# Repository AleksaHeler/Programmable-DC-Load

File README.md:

# Programmable DC Load

Flexible programmable DC constant current/power load using Arduin Nano and a custom PCB.

Following some ideas from [this YouTube playlist](https://www.youtube.com/playlist?list=PLUMG8JNssPPzbr4LydbTcBrhoPlemu5Dt) from [Scullcom Hobby Electronics](https://www.youtube.com/@scullcomhobbyelectronics1702).

## PCB design and schematic

## Finished device in enclosure

## Programming the ATmega328P

### Setting the fuses

If you just want the same ones as used in a standard Arduino, you can find them in the ```boards.txt``` file:
```
uno.bootloader.low_fuses=0xff
uno.bootloader.high_fuses=0xde
uno.bootloader.extended_fuses=0x05
```

We will be using another Arduino as ISP, so we should first program it with given example code, then we can use avrdude option 'avrisp', and use the port number of that device. We can read the fuses, and check if conncections are ok with:
``` 
.\utils\avrdude-v8.0\avrdude.exe -c avrisp -p m328p -P com23 -b 19200 -U lfuse:r:-:i -U hfuse:r:-:i -U efuse:r:-:i -v
``` 

So for these default settings we would use the following command:
``` 
.\utils\avrdude-v8.0\avrdude.exe -c avrisp -p m328p -P com23 -b 19200 -U lfuse:w:0xFF:m -U hfuse:w:0xDE:m -U efuse:w:0x05:m -v
```
Where:
```
  -c <programmer>                          Specify programmer type.
  -p <partno>                              Required. Specify AVR device.
  -P <port>                                Specify connection port.
  -b <baudrate>                            Override RS-232 baud rate.
  -U <memtype>:r|w|v:<filename>[:format]   Memory operation specification.
  -v                                       Verbose output. -v -v for more.
```
More options info can be found [here](https://www.nongnu.org/avrdude/user-manual/avrdude_3.html).

### Burning the bootloader

To burn the bootloader, we will also be using Arduino as ISP, and in Arduino software just select burn bootloader after we select the board as Arduino Uno.

### Flashing the program

???

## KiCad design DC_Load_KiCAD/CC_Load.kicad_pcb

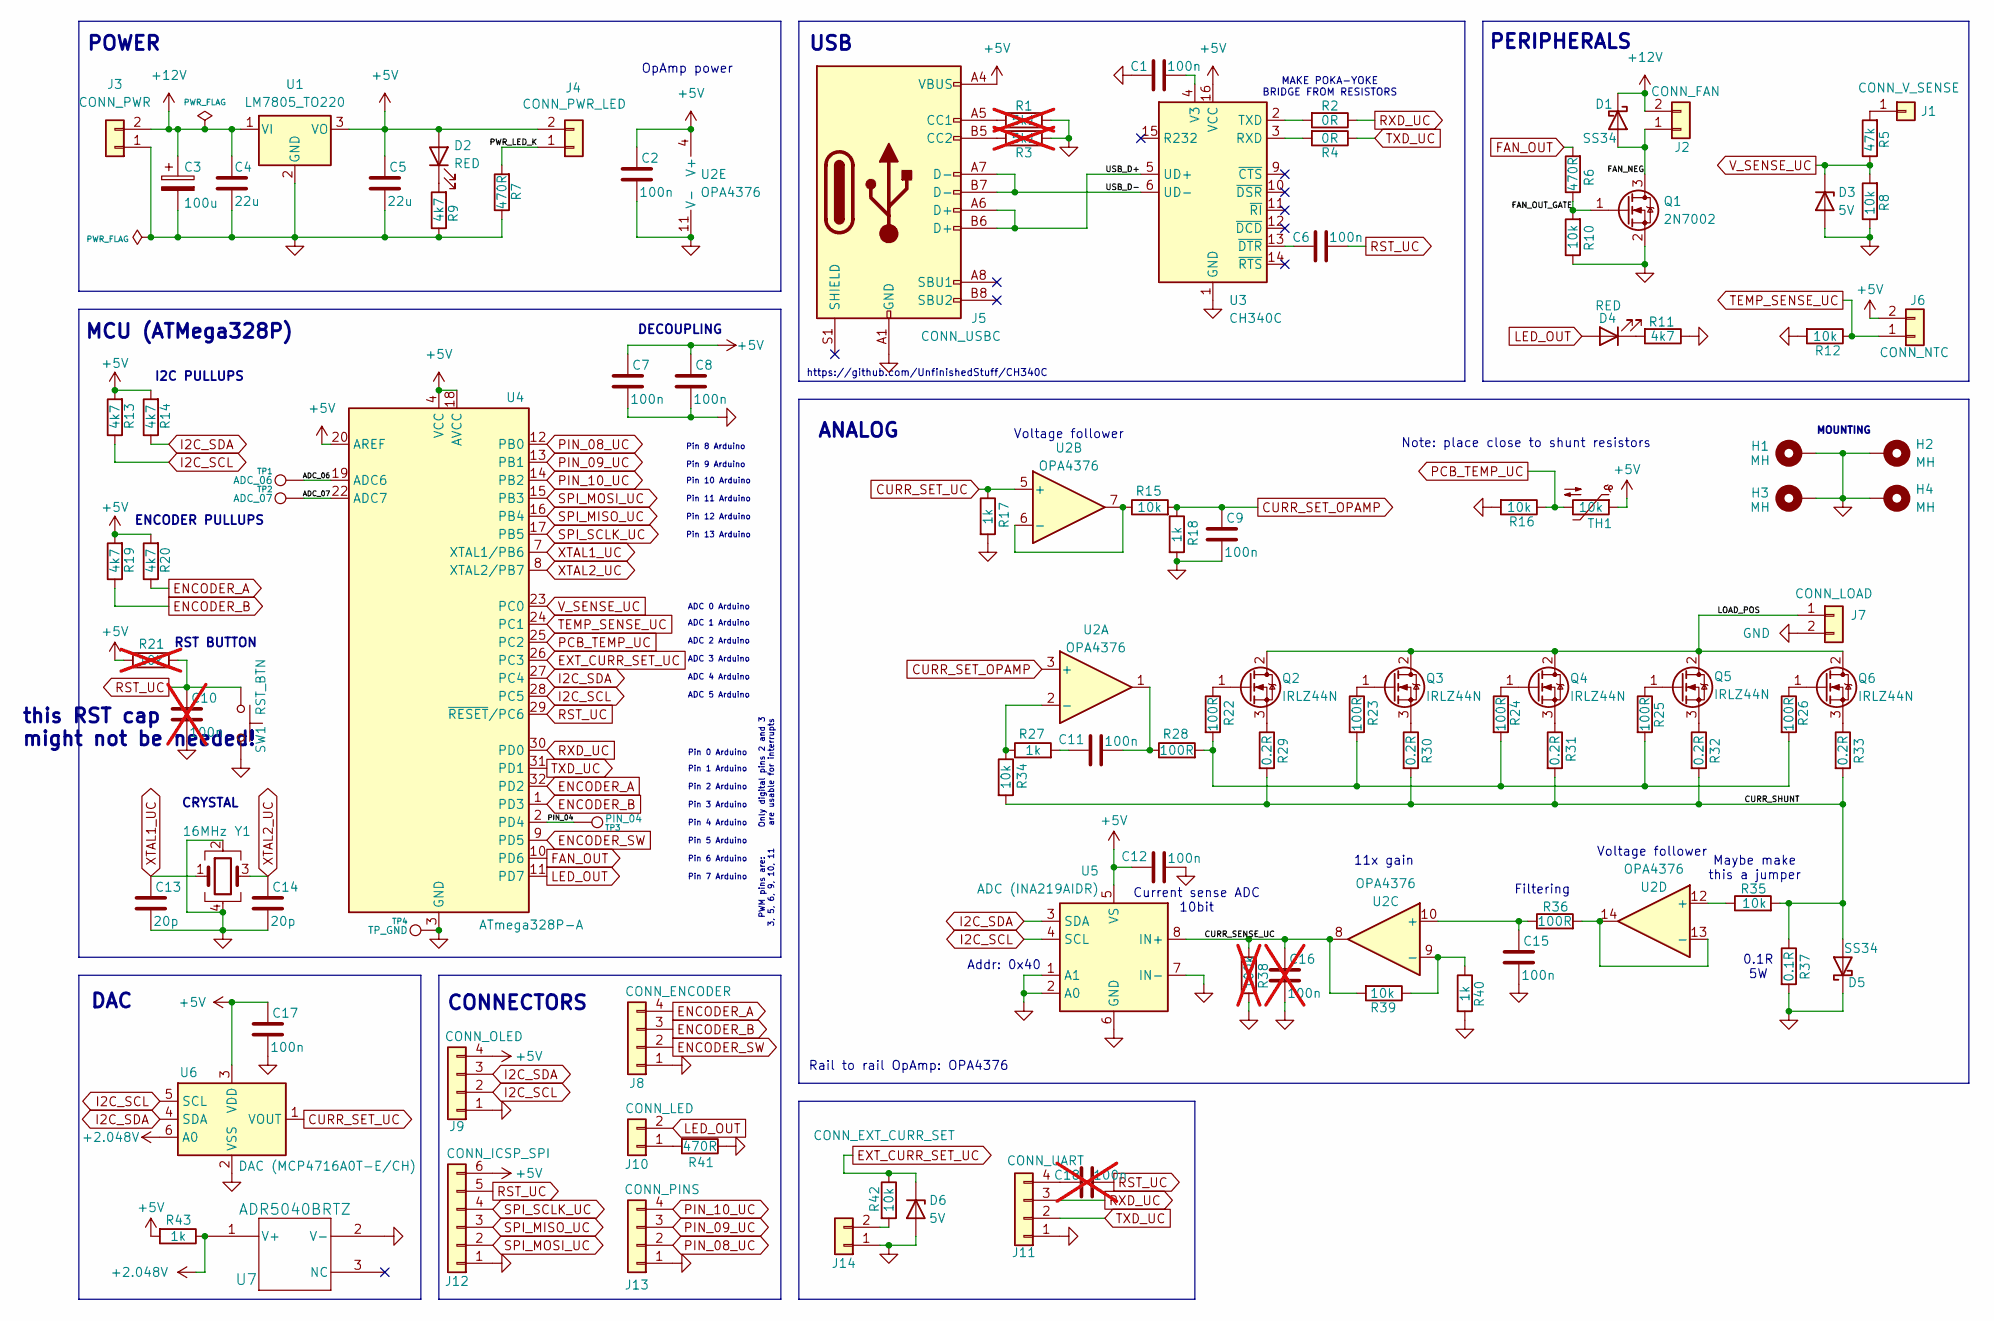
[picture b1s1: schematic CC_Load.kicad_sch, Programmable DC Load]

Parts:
C1, C2, C6, C7, C8, C9, C11, C12, C15, C17: 100n; C_1206_3216Metric
C3: 100u; CP_Elec_8x10.5
C4, C5: 22u; C_0805_2012Metric
C10, C16, C18: 100n; C_1206_3216Metric; not fitted
C13, C14: 20p; C_0805_2012Metric
D1, D5: SS34; D_SMA
D2, D4: RED; LED_1210_3225Metric
D3, D6: 5V; D_SOD-123
H1, H2, H3, H4: MH; MountingHole_3.2mm_M3_Pad
J1: CONN_V_SENSE; PinHeader_1x01_P2.54mm_Vertical
J2: CONN_FAN; PinHeader_1x02_P2.54mm_Vertical
J3: CONN_PWR; PinHeader_1x02_P2.54mm_Vertical
J4: CONN_PWR_LED; PinHeader_1x02_P2.54mm_Vertical
J5: CONN_USBC; USB_C_Receptacle_G-Switch_GT-USB-7010ASV
J6: CONN_NTC; PinHeader_1x02_P2.54mm_Vertical
J7: CONN_LOAD; PinHeader_1x02_P2.54mm_Vertical
J8: CONN_ENCODER; PinHeader_1x04_P2.54mm_Vertical
J9: CONN_OLED; PinHeader_1x04_P2.54mm_Vertical
J10: CONN_LED; PinHeader_1x02_P2.54mm_Vertical
J11: CONN_UART; PinHeader_1x04_P2.54mm_Vertical
J12: CONN_ICSP_SPI; PinHeader_1x06_P2.54mm_Vertical
J13: CONN_PINS; PinHeader_1x04_P2.54mm_Vertical
J14: CONN_EXT_CURR_SET; PinHeader_1x02_P2.54mm_Vertical
Q1: 2N7002; SOT-23
Q2, Q3, Q4, Q5, Q6: IRLZ44N; TO-220-3_Vertical
R1, R3: 5k1; R_0805_2012Metric; not fitted
R2, R4: 0R; R_1206_3216Metric
R5: 47k; R_1206_3216Metric
R6, R7, R41: 470R; R_1206_3216Metric
R8, R10, R12, R15, R16, R34, R35, R39, R42: 10k; R_1206_3216Metric
R9, R11, R13, R14, R19, R20: 4k7; R_1206_3216Metric
R17, R18, R27, R40, R43: 1k; R_1206_3216Metric
R21: 10k; R_1206_3216Metric; not fitted
R22, R23, R24, R25, R26, R28, R36: 100R; R_1206_3216Metric
R29, R30, R31, R32, R33: 0.2R; R_1206_3216Metric
R37: 0.1R; R_Axial_Power_L25.0mm_W9.0mm_P27.94mm
R38: 100k; R_1206_3216Metric; not fitted
SW1: RST_BTN; SW_PUSH_6mm
TH1: 10k; R_0805_2012Metric
TP1: ADC_06; TestPoint_THTPad_1.5x1.5mm_Drill0.7mm
TP2: ADC_07; TestPoint_THTPad_1.5x1.5mm_Drill0.7mm
TP3: PIN_04; TestPoint_THTPad_1.5x1.5mm_Drill0.7mm
TP4: TP_GND; TestPoint_THTPad_1.5x1.5mm_Drill0.7mm
U1: LM7805_TO220; TO-220-3_Vertical
U2: OPA4376; TSSOP-14_4.4x5mm_P0.65mm
U3: CH340C; SOIC-16_3.9x9.9mm_P1.27mm
U4: ATmega328P-A; TQFP-32_7x7mm_P0.8mm
U5: ADC (INA219AIDR); SOIC-8_3.9x4.9mm_P1.27mm
U6: DAC (MCP4716A0T-E/CH); SOT-23-6
U7: ADR5040BRTZ; SOT-23
Y1: 16MHz; Crystal_SMD_3225-4Pin_3.2x2.5mm

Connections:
+2.048V: R43.1, U6.6 (A0), U7.1 (V+)
+5V: C2.1, C5.1, C7.1, C8.1, C12.1, C17.1, D2.2 (A), J4.2, J5.A4 (VBUS), J5.A9 (VBUS), J5.B4 (VBUS), J5.B9 (VBUS), J6.2, J9.4, J12.6, R13.2, R14.2, R19.2, R20.2, R21.2, R43.2, TH1.1, U1.3 (VO), U2.4 (V+), U3.16 (VCC), U4.4 (VCC), U4.6 (VCC), U4.18 (AVCC), U4.20 (AREF), U5.5 (VS), U6.3 (VDD)
+12V: C3.1, C4.1, D1.1 (K), J2.2, J3.2, U1.1 (VI)
/ADC_06: TP1.1, U4.19 (ADC6)
/ADC_07: TP2.1, U4.22 (ADC7)
/CURR_SENSE_UC: C16.1, R38.1, R39.2, U2.8, U5.8 (IN+)
/CURR_SHUNT: D5.2 (A), R29.2, R30.2, R31.2, R32.2, R33.2, R34.2, R35.2, R37.1
/FAN_NEG: D1.2 (A), J2.1, Q1.3 (D)
/FAN_OUT_GATE: Q1.1 (G), R6.1, R10.2
/LOAD_POS: J7.1, Q2.2 (D), Q3.2 (D), Q4.2 (D), Q5.2 (D), Q6.2 (D)
/PIN_04: TP3.1, U4.2 (PD4)
/PWR_LED_K: J4.1, R7.2
/USB_D+: J5.A6 (D+), J5.B6 (D+), U3.5 (UD+)
/USB_D-: J5.A7 (D-), J5.B7 (D-), U3.6 (UD-)
CURR_SET_OPAMP: C9.1, R15.2, R18.1, U2.3 (+)
CURR_SET_UC: R17.1, U2.5 (+), U6.1 (VOUT)
ENCODER_A: J8.4, R20.1, U4.32 (PD2)
ENCODER_B: J8.3, R19.1, U4.1 (PD3)
ENCODER_SW: J8.2, U4.9 (PD5)
EXT_CURR_SET_UC: D6.1 (K), R42.1, U4.26 (PC3)
FAN_OUT: R6.2, U4.10 (PD6)
GND: C1.1, C2.2, C3.2, C4.2, C5.2, C7.2, C8.2, C9.2, C10.2, C12.2, C13.2, C14.2, C15.2, C16.2, C17.2, D3.2 (A), D5.1 (K), D6.2 (A), H1.1, H2.1, H3.1, H4.1, J3.1, J5.A1 (GND), J5.A12 (GND), J5.B1 (GND), J5.B12 (GND), J7.2, J8.1, J9.1, J11.1, J12.1, J13.1, J14.1, Q1.2 (S), R1.1, R3.1, R7.1, R8.1, R9.1, R10.1, R11.1, R12.2, R16.2, R17.2, R18.2, R37.2, R38.2, R40.2, R41.1, SW1.2, TP4.1, U1.2 (GND), U2.11 (V-), U3.1 (GND), U4.3 (GND), U4.5 (GND), U4.21 (GND), U5.1 (A1), U5.2 (A0), U5.6 (GND), U5.7 (IN-), U6.2 (VSS), U7.2 (V-), Y1.2, Y1.4
I2C_SCL: J9.2, R13.1, U4.28 (PC5), U5.4 (SCL), U6.5 (SCL)
I2C_SDA: J9.3, R14.1, U4.27 (PC4), U5.3 (SDA), U6.4 (SDA)
LED_OUT: D4.2 (A), J10.2, U4.11 (PD7)
unnamed: C11.1, R27.2
unnamed: C11.2, R28.1, U2.1
unnamed: D2.1 (K), R9.2
unnamed: D4.1 (K), R11.2
unnamed: J1.1, R5.2
unnamed: J5.A5 (CC1), R1.2
unnamed: J5.B5 (CC2), R3.2
unnamed: J10.1, R41.2
unnamed: C18.1, J11.4
unnamed: J14.2, R42.2
unnamed: Q2.1 (G), R22.1
unnamed: Q2.3 (S), R29.1
unnamed: Q3.1 (G), R23.1
unnamed: Q3.3 (S), R30.1
unnamed: Q4.1 (G), R24.1
unnamed: Q4.3 (S), R31.1
unnamed: Q5.1 (G), R25.1
unnamed: Q5.3 (S), R32.1
unnamed: Q6.1 (G), R26.1
unnamed: Q6.3 (S), R33.1
unnamed: R22.2, R23.2, R24.2, R25.2, R26.2, R28.2
unnamed: R27.1, R34.1, U2.2 (-)
unnamed: R15.1, U2.6 (-), U2.7
unnamed: C15.1, R36.1, U2.10 (+)
unnamed: R39.1, R40.1, U2.9 (-)
unnamed: R35.1, U2.12 (+)
unnamed: R36.2, U2.13 (-), U2.14
unnamed: R4.2, U3.3 (RXD)
unnamed: R2.2, U3.2 (TXD)
unnamed: C1.2, U3.4 (V3)
unnamed: C6.1, U3.13 (~DTR)
PCB_TEMP_UC: R16.1, TH1.2, U4.25 (PC2)
PIN_08_UC: J13.2, U4.12 (PB0)
PIN_09_UC: J13.3, U4.13 (PB1)
PIN_10_UC: J13.4, U4.14 (PB2)
RST_UC: C6.2, C10.1, C18.2, J12.5, R21.1, SW1.1, U4.29 (~RESET/PC6)
RXD_UC: J11.3, R2.1, U4.30 (PD0)
SPI_MISO_UC: J12.3, U4.16 (PB4)
SPI_MOSI_UC: J12.2, U4.15 (PB3)
SPI_SCLK_UC: J12.4, U4.17 (PB5)
TEMP_SENSE_UC: J6.1, R12.1, U4.24 (PC1)
TXD_UC: J11.2, R4.1, U4.31 (PD1)
V_SENSE_UC: D3.1 (K), R5.1, R8.2, U4.23 (PC0)
XTAL1_UC: C13.1, U4.7 (XTAL1/PB6), Y1.1
XTAL2_UC: C14.1, U4.8 (XTAL2/PB7), Y1.3

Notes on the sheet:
DAC
Pin 12 Arduino
ANALOG
Pin 10 Arduino
ENCODER PULLUPS
POWER
Rail to rail OpAmp: OPA4376
Pin 0 Arduino
OpAmp power
Pin 8 Arduino
DECOUPLING
I2C PULLUPS
Only digital pins 2 and 3 are usable for interrupts
Pin 2 Arduino
Voltage follower
https://github.com/UnfinishedStuff/CH340C
Pin 13 Arduino
Current sense ADC 10bit
CRYSTAL
PWM pins are: 3, 5, 6, 9, 10, 11
Pin 7 Arduino
Pin 4 Arduino
ADC 1 Arduino
MAKE POKA-YOKE BRIDGE FROM RESISTORS
USB
ADC 4 Arduino
ADC 0 Arduino
this RST cap might not be needed!
CONNECTORS
PERIPHERALS
ADC 3 Arduino
Pin 9 Arduino
Addr: 0x40
ADC 5 Arduino
Filtering
ADC 2 Arduino
RST BUTTON
MOUNTING
0.1R 5W
Pin 11 Arduino

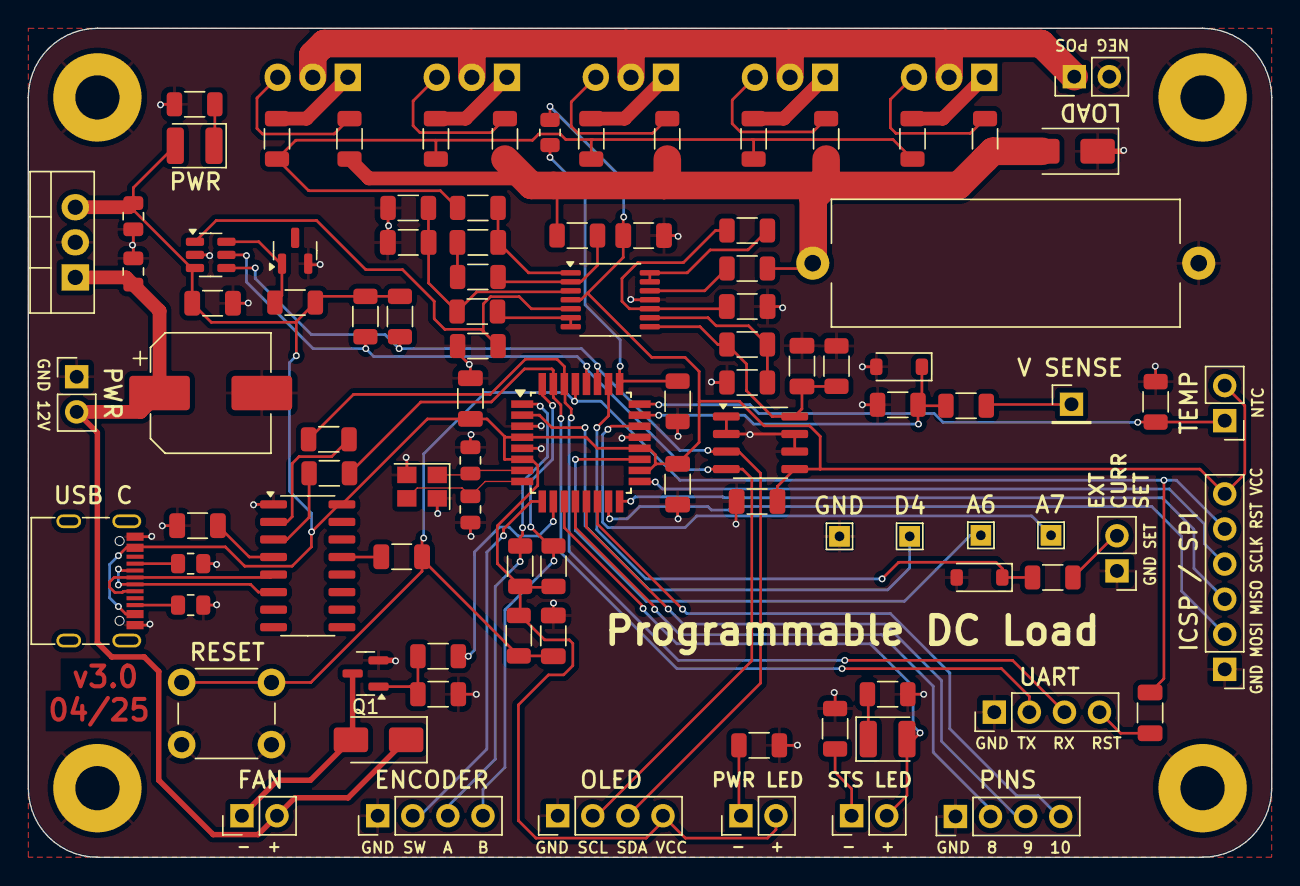
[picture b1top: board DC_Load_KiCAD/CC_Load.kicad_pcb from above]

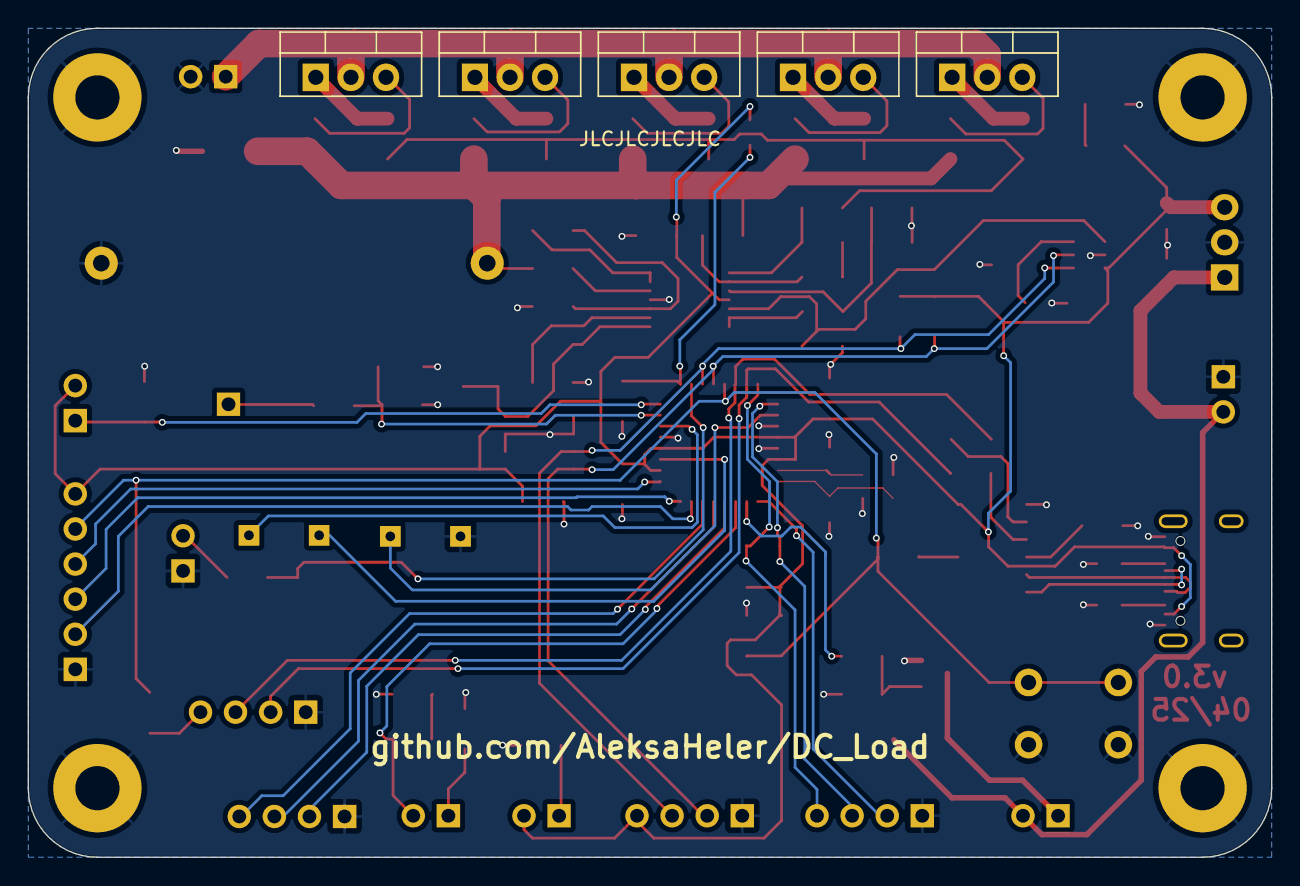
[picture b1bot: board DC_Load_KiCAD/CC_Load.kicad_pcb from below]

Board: 2 copper layers, 90.0 x 60.0 mm, 105 parts (5 on the bottom side), 70 nets.

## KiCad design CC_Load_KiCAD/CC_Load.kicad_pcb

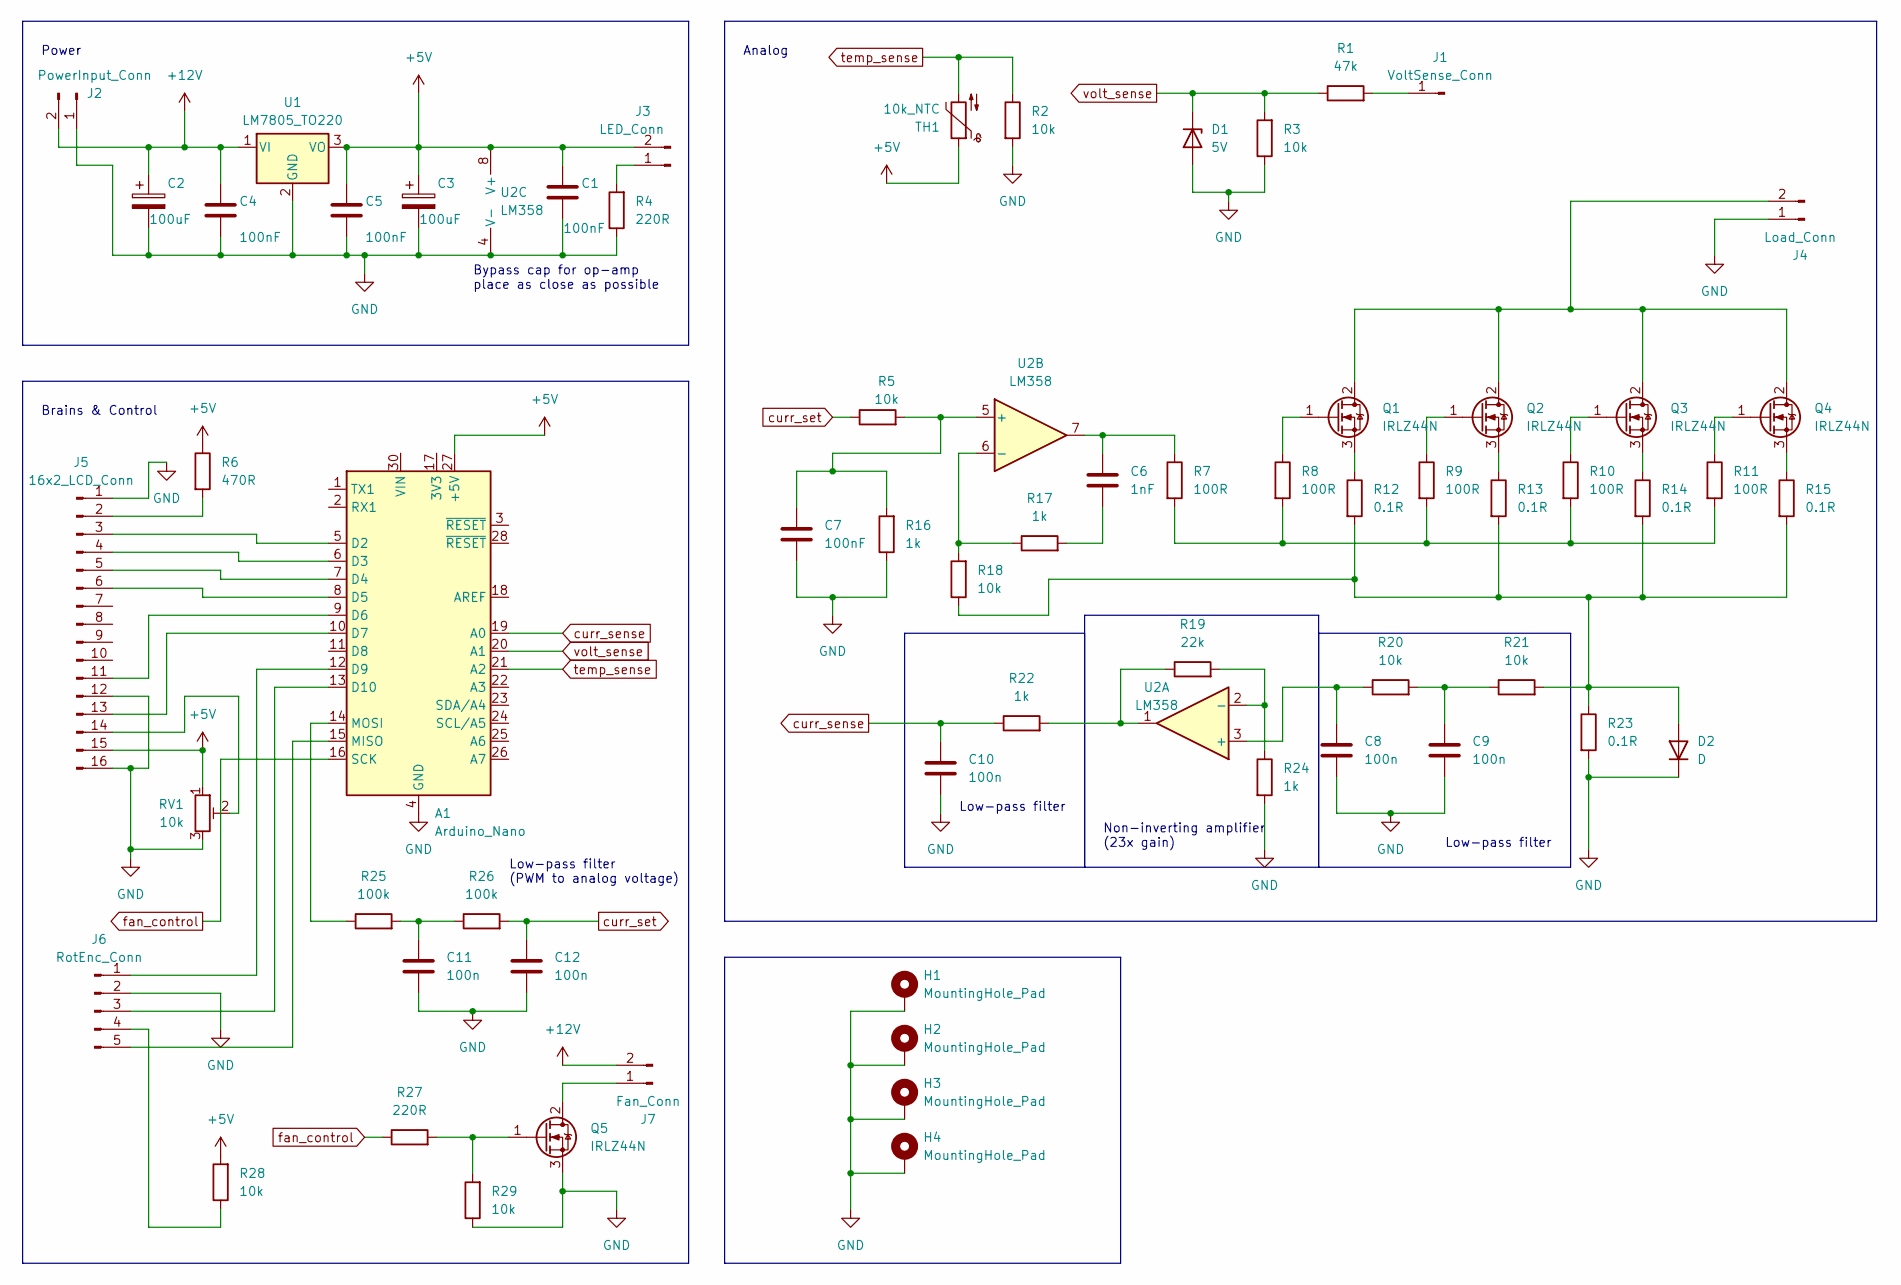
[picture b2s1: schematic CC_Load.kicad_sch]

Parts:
A1: Arduino_Nano
C1, C4, C5, C7: 100nF; C_1206_3216Metric
C2, C3: 100uF; CP_Radial_D6.3mm_P2.50mm
C6: 1nF; C_1206_3216Metric
C8, C9, C10, C11, C12: 100n; C_1206_3216Metric
D1: 5V; D_T-1_P5.08mm_Horizontal
D2: D; D_T-1_P5.08mm_Horizontal
H1, H2, H3, H4: MountingHole_Pad; MountingHole_3.2mm_M3_Pad
J1: VoltSense_Conn; ScrewTerminal_01x02_P5mm
J2: PowerInput_Conn; ScrewTerminal_01x02_P5mm
J3: LED_Conn; PinHeader_1x02_P2.54mm_Vertical
J4: Load_Conn; ScrewTerminal_01x02_P5mm
J5: 16x2_LCD_Conn; PinHeader_1x16_P2.54mm_Vertical
J6: RotEnc_Conn; PinHeader_1x05_P2.54mm_Vertical
J7: Fan_Conn; PinHeader_1x02_P2.54mm_Vertical
Q1, Q2, Q3, Q4, Q5: IRLZ44N; TO-220-3_Vertical
R1: 47k; R_1206_3216Metric
R2, R3, R5, R18, R20, R21, R28, R29: 10k; R_1206_3216Metric
R4, R27: 220R; R_1206_3216Metric
R6: 470R; R_1206_3216Metric
R7, R8, R9, R10, R11: 100R; R_1206_3216Metric
R12, R13, R14, R15, R23: 0.1R; R_Axial_Power_L25.0mm_W9.0mm_P27.94mm
R16, R17, R22, R24: 1k; R_1206_3216Metric
R19: 22k; R_1206_3216Metric
R25, R26: 100k; R_1206_3216Metric
RV1: 10k; PinHeader_1x03_P2.54mm_Vertical
TH1: 10k_NTC; PinHeader_1x02_P2.54mm_Vertical
U1: LM7805_TO220; TO-220-3_Vertical
U2: LM358; DIP-8_W7.62mm_LongPads

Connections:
+5V: A1.27 (+5V), C1.1, C3.1, C5.1, J3.2, J5.15, R6.1, R28.2, RV1.1, TH1.1, U1.3 (VO), U2.8 (V+); also elsewhere on the board
+12V: C2.1, C4.1, J2.2, J7.2, U1.1 (VI)
GND: A1.4 (GND), A1.29 (GND), C1.2, C2.2, C3.2, C4.2, C5.2, C7.2, C8.2, C9.2, C10.2, C11.2, C12.2, D1.2 (A), D2.1 (K), H1.1, H2.1, H3.1, H4.1, J2.1, J4.1, J5.1, J5.12, J5.16, J6.2, Q5.3 (S), R2.2, R3.1, R4.1, R16.1, R23.2, R24.2, R29.1, RV1.3, U1.2 (GND), U2.4 (V-); also elsewhere on the board
unnamed: A1.5 (D2), J5.3
unnamed: A1.6 (D3), J5.4
unnamed: A1.7 (D4), J5.5
unnamed: A1.8 (D5), J5.6
unnamed: A1.9 (D6), J5.11
unnamed: A1.10 (D7), J5.13
unnamed: A1.12 (D9), J6.1
unnamed: A1.13 (D10), J6.3
unnamed: A1.15 (MISO), J6.5
unnamed: A1.14 (MOSI), R25.1
unnamed: C6.1, R7.1, U2.7
unnamed: C6.2, R17.2
unnamed: C9.1, R20.2, R21.1
unnamed: C11.1, R25.2, R26.1
unnamed: D2.2 (A), R12.2, R13.2, R14.2, R15.2, R18.1, R21.2, R23.1
unnamed: J1.1, R1.2
unnamed: J3.1, R4.2
unnamed: J4.2, Q1.2 (D), Q2.2 (D), Q3.2 (D), Q4.2 (D)
unnamed: J5.2, R6.2
unnamed: J5.14, RV1.2
unnamed: J6.4, R28.1
unnamed: J7.1, Q5.2 (D)
unnamed: Q1.1 (G), R8.1
unnamed: Q1.3 (S), R12.1
unnamed: Q2.1 (G), R9.1
unnamed: Q2.3 (S), R13.1
unnamed: Q3.1 (G), R10.1
unnamed: Q3.3 (S), R14.1
unnamed: Q4.1 (G), R11.1
unnamed: Q4.3 (S), R15.1
unnamed: Q5.1 (G), R27.2, R29.2
unnamed: R7.2, R8.2, R9.2, R10.2, R11.2
unnamed: R19.1, R22.2, U2.1
unnamed: C8.1, R20.1, U2.3 (+)
unnamed: R19.2, R24.1, U2.2 (-)
unnamed: C7.1, R5.2, R16.2, U2.5 (+)
unnamed: R17.1, R18.2, U2.6 (-)
curr_sense: A1.19 (A0), C10.1, R22.1
curr_set: C12.1, R5.1, R26.2
fan_control: A1.16 (SCK), R27.1
temp_sense: A1.21 (A2), R2.1, TH1.2
volt_sense: A1.20 (A1), D1.1 (K), R1.1, R3.2

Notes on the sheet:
Low-pass filter (PWM to analog voltage)
Bypass cap for op-amp place as close as possible
Low-pass filter
Non-inverting amplifier (23x gain)
Brains & Control
Analog
Power

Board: 2 copper layers, 65 parts (0 on the bottom side), 45 nets, no tracks yet.

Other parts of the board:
C5#2: 100nF; C_1206_3216Metric

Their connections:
+5V: C5#2.1; also elsewhere on the board
GND: C5#2.2; also elsewhere on the board

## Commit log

2023-10-29 Started making the schematic
2023-11-28 Create a whole new schematic for this project
2023-11-29 Finished first design for my DIY PCB
2023-11-30 Changed PCB design, will order from JLCPCB
2023-12-08 Add DIY PCB version for initial testing
2023-12-12 Update schematic and code
2023-12-16 Update both code and kicad
2024-05-02 Update PCB and prepare for ordering
2024-05-17 Final review and order from JLCPCB
2024-10-19 Add images
2025-04-23 Added comments for future improvements, successfully flashed one device
2025-04-23 Update initial code with simple drivers
2025-04-25 Update PCB to ver 3.0, in code updatet drivers a bit
